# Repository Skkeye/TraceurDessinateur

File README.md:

# TraceurDessinateur
Projet Final Cegep

## Contexte/Origine
Le dessin est un art qui est difficile à apprendre et à maîtriser, alors l’option de prendre une photo pour décrire une scène devient très intéressante pour un artiste dépourvu de talent de dessinateur. Le TraceurDessinateur entre en jeu pour donner un compromis entre le dessin et la photo.

## Besoin General
Le besoin est de pouvoir dessiner un ou des objets sans pour autant avoir du talent pour dessiner. La partie cadrage et pinceau doivent être sans fil et rechargeable et doivent pouvoir être utilisés dans la majorité des environnements. La partie dessinateur doit être capable d'être configurable et facile à utiliser. 

## Objectif
L’objectif ici est de concevoir et de réaliser un pinceau 3d et une caméra de cadrage connectée par wifi au dessinateur qui lui pourra dessiner sur une feuille de papier.

## Fonctions Principales
La solution aura 3 parties principales en plus de la partie serveur qui connectera le tout. La première partie consiste d’une manette connectée au serveur par wifi, la deuxième d’une caméra qui détecte la position de la manette et la troisième d’un système de moteurs pas-à-pas pour dessiner sur une feuille de papier.
- La solution doit pouvoir voir et trouver la position de la manette via une caméra.
- La solution doit pouvoir choisir la couleur de la manette en fonction des couleurs perçus par la caméra.
- La solution doit pouvoir capter une force variable avec la manette.
- La solution doit consister d’une manette et d’une caméra portatives.
- La solution doit consister d’une manette et d’une caméra qui se connectent à un serveur WiFi dédié.
- La solution doit pouvoir dessiner à l'aide d’une machine CNC 2.5 axes.
- La solution doit être configurable via un menu contrôle avec un encodeur de rotation avec bouton.
- La solution doit avoir une caméra pour aider à positionner la caméra.
- La solution doit pouvoir être alimentée par une cellule LiPo pour la manette et la caméra.
- La solution doit avoir un bouton Marche/Arret sur le Dessinateur, la Caméra et la Manette.

## Contraintes
- Tension d’alimentation principale : 120 VAC
- Tension d’alimentation moteurs pas à pas : 4.1 VDC
- Tension d’alimentation de la caméra et la manette : 3.3v (LiPo 3.7v)
- Connexion sans fils : WiFi
- Application sur microcontrôleurs

## Livrables
- Produits Assembles : Manette, Camera, Dessinateur
- Logiciels installés sur les microcontrolleurs

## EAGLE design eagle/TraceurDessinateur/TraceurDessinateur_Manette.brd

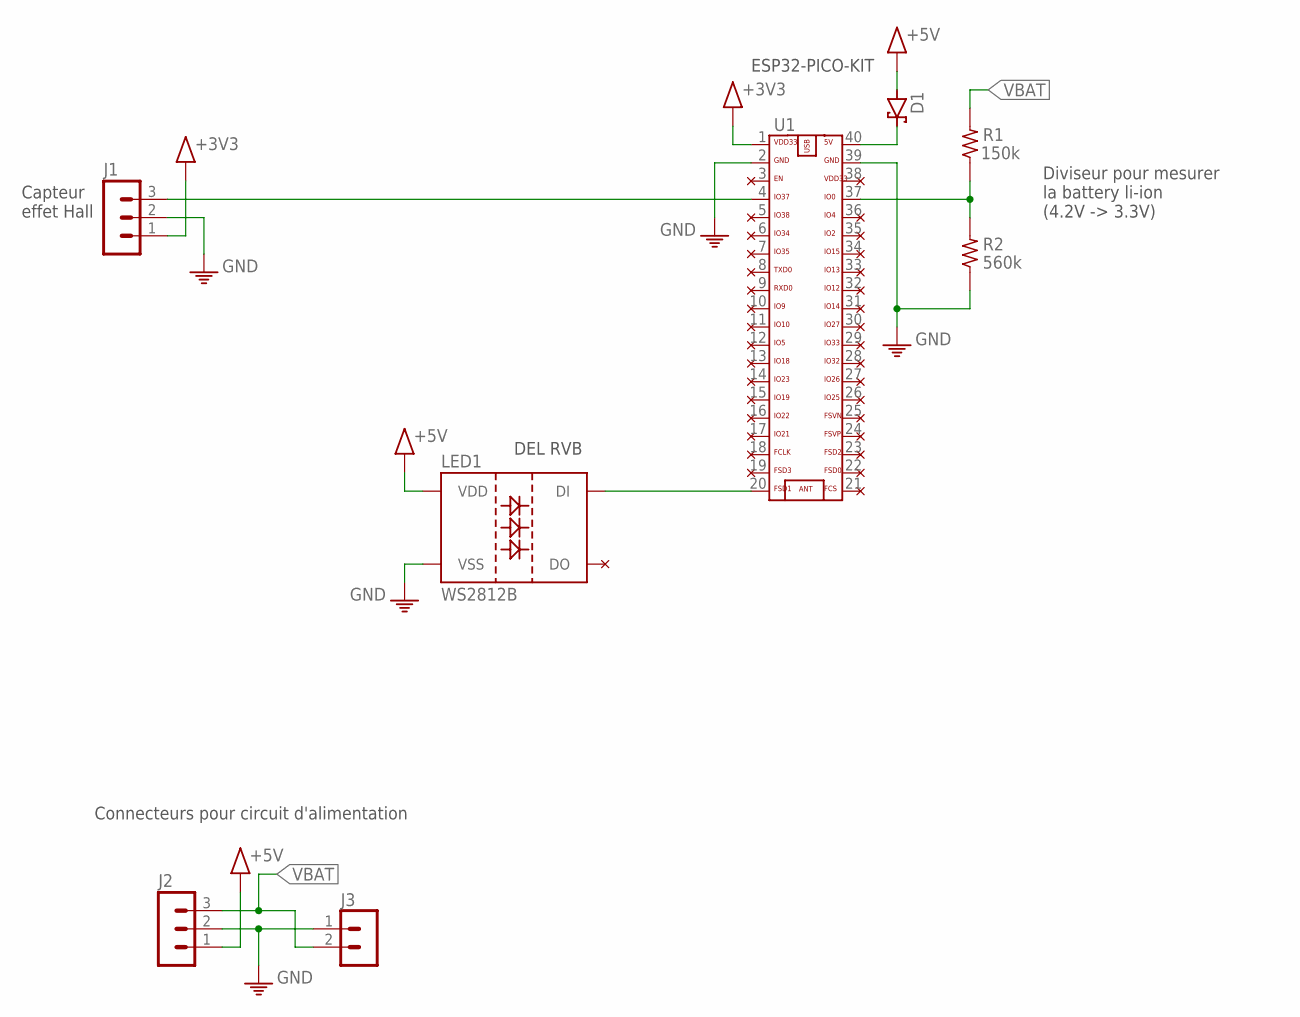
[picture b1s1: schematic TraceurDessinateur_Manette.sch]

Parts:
D1: 1N5817-B; DO41-7.6
J1, J2: MA03-1
J3: B2B-PH-K
LED1: WS2812B
R1: 150k; R1206W
R2: 560k; R1206W
U1: ESP32-PICO-V4-SOCKET

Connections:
+3V3: J1.1, U1.1 (3V3)
+5V: D1.A, J2.1, LED1.1 (VDD)
ADC_HALL: J1.3, U1.4
GND: J1.2, J2.2, J3.1, LED1.3 (VSS), R2.1, U1.2, U1.39
LED_DATA: LED1.4 (DI), U1.20
unnamed: D1.C, U1.40
VBAT: J2.3, J3.2, R1.2
VSENSE: R1.1, R2.2, U1.37

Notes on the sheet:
Capteur effet Hall
Connecteurs pour circuit d'alimentation
Diviseur pour mesurer la battery li-ion (4.2V -> 3.3V)
DEL RVB
ESP32-PICO-KIT

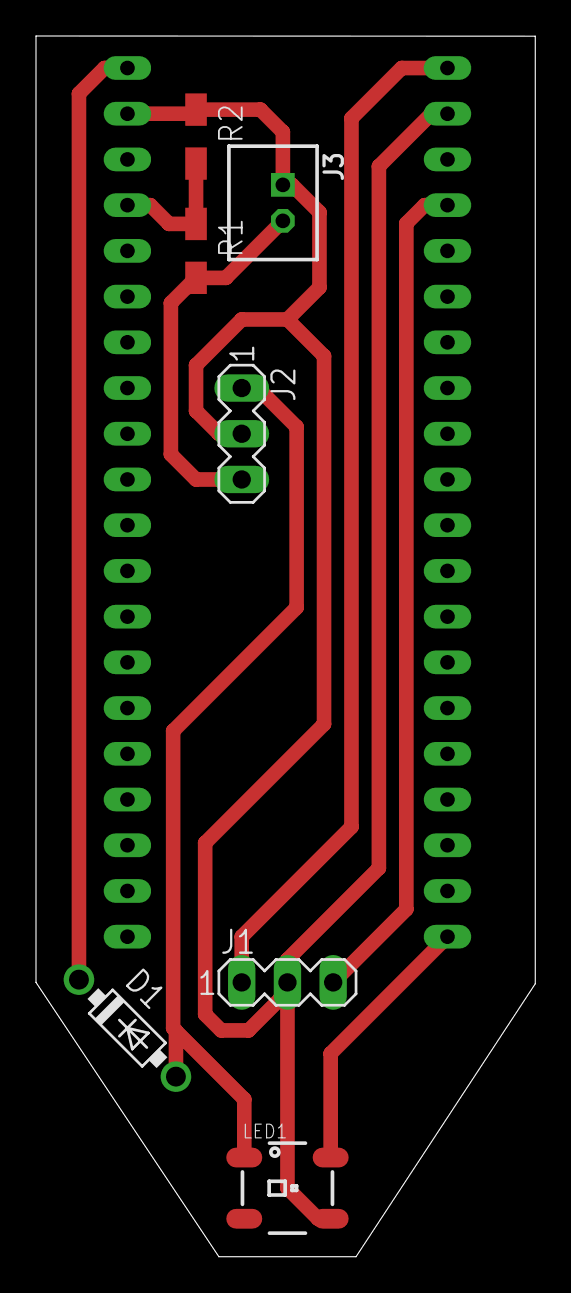
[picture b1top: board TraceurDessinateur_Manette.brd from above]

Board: 2 copper layers, 27.7 x 67.8 mm, 9 parts (1 on the bottom side), 8 nets.

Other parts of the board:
U$35: A3L-LOC

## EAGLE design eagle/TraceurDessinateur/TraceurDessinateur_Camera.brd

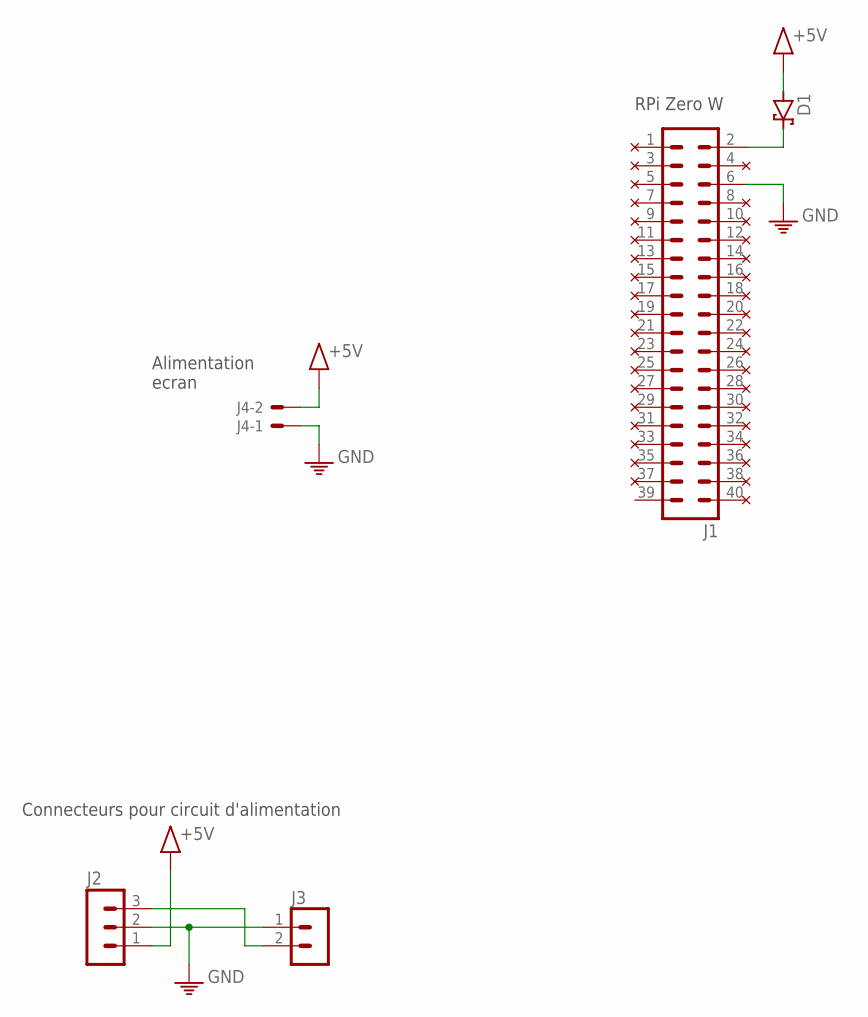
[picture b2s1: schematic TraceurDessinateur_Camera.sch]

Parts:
D1: 1N5817-B; DO41-7.6
J1: MA20-2
J2: MA03-1
J3: B2B-PH-K
J4: 22-23-2021

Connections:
+5V: D1.A, J2.1, J4.2
GND: J1.6, J2.2, J3.1, J4.1
unnamed: D1.C, J1.2
VBAT: J2.3, J3.2

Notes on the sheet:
RPi Zero W
Connecteurs pour circuit d'alimentation
Alimentation ecran

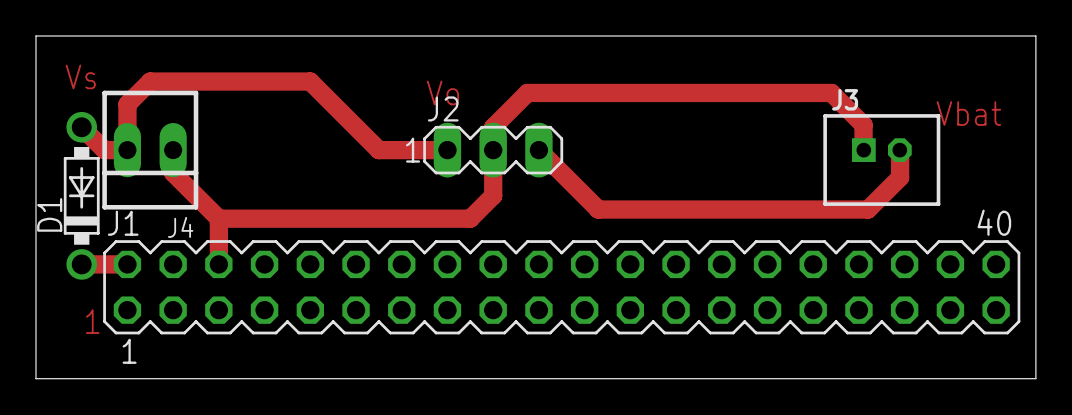
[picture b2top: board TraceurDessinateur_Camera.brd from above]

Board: 2 copper layers, 55.5 x 19.0 mm, 6 parts (0 on the bottom side), 4 nets.

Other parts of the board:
U$37: A3L-LOC

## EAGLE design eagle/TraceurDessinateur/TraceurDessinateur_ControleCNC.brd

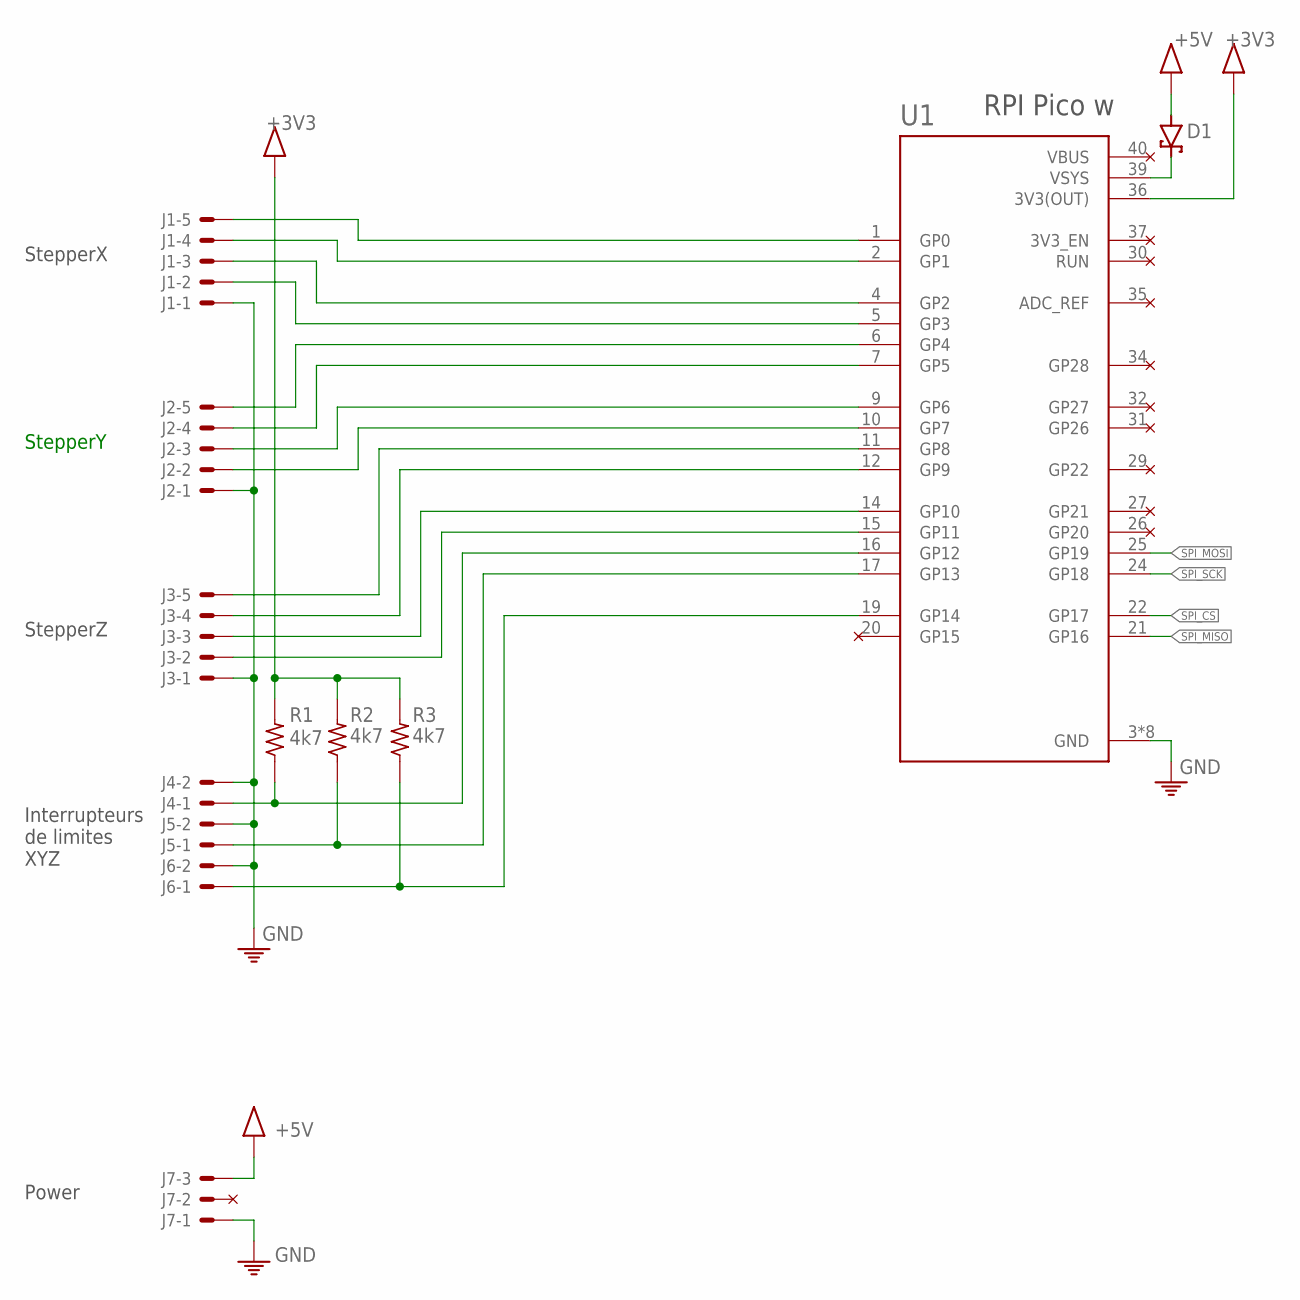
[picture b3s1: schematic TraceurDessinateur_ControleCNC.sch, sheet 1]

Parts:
D1: 1N5817-B; DO41-7.6
J1, J2, J3: 22-23-2051
J4, J5, J6: 22-23-2021
J7: 22-23-2031
R1, R2, R3: 4k7; R1206
U1: RASPBERRY_PICO-HEADERS-NO_DEBUGPICO-PKG-TH-NO_DEB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; PICO-PKG-TH-NO_DEBUG

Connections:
+3V3: R1.2, R2.2, R3.2, U1.36 (3V3(OUT)); also elsewhere on the board
+5V: D1.A, J7.3; also elsewhere on the board
GND: J1.1, J2.1, J3.1, J4.2, J5.2, J6.2, J7.1, U1.3 (GND), U1.8 (GND), U1.13 (GND), U1.18 (GND), U1.23 (GND), U1.28 (GND), U1.33 (GND), U1.38 (GND); also elsewhere on the board
unnamed: J1.5, U1.1 (GP0)
unnamed: J1.4, U1.2 (GP1)
unnamed: J1.3, U1.4 (GP2)
unnamed: J1.2, U1.5 (GP3)
unnamed: J2.5, U1.6 (GP4)
unnamed: J2.4, U1.7 (GP5)
unnamed: J2.3, U1.9 (GP6)
unnamed: J2.2, U1.10 (GP7)
unnamed: J3.5, U1.11 (GP8)
unnamed: J3.4, U1.12 (GP9)
unnamed: J3.3, U1.14 (GP10)
unnamed: J3.2, U1.15 (GP11)
unnamed: J4.1, R1.1, U1.16 (GP12)
unnamed: J5.1, R2.1, U1.17 (GP13)
unnamed: J6.1, R3.1, U1.19 (GP14)
unnamed: D1.C, U1.39 (VSYS)
SPI_CS: U1.22 (GP17); also elsewhere on the board
SPI_MISO: U1.21 (GP16); also elsewhere on the board
SPI_MOSI: U1.25 (GP19); also elsewhere on the board
SPI_SCK: U1.24 (GP18); also elsewhere on the board

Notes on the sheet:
StepperX
StepperY
StepperZ
Interrupteurs de limites XYZ
RPI Pico w
Power

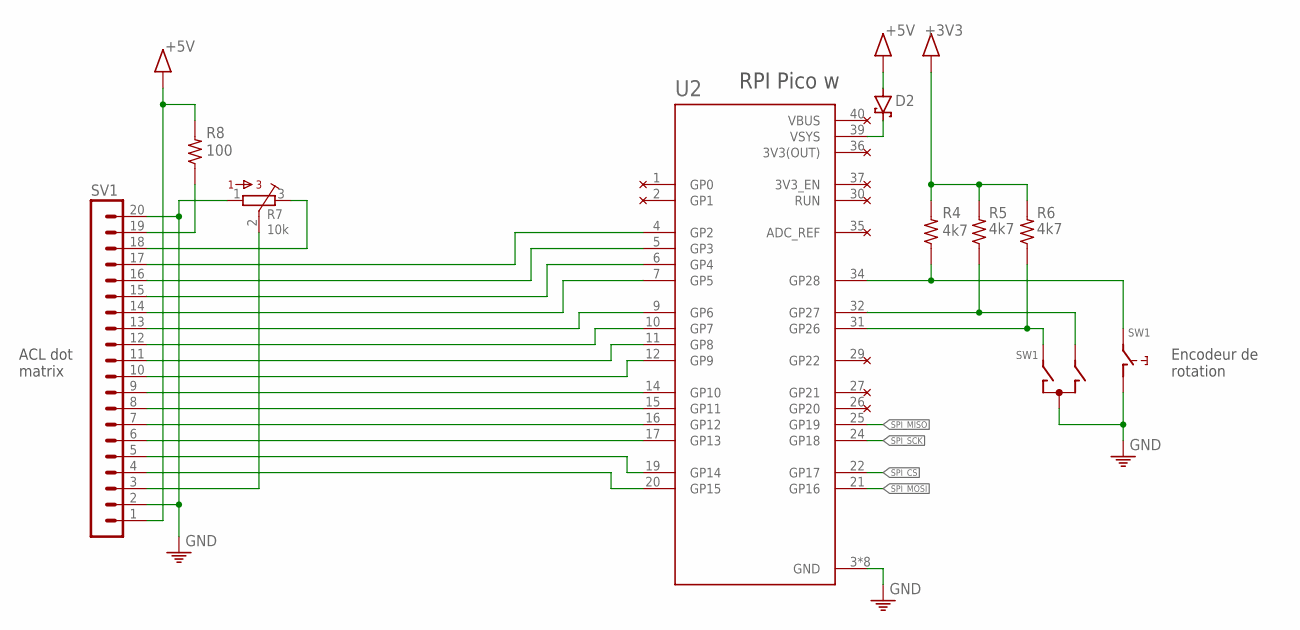
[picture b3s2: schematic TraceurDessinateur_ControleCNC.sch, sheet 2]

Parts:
D2: 1N5817-B; DO41-7.6
R4, R5, R6: 4k7; R1206
R7: 10k; 3362P
R8: 100; R1206
SV1: MA20-1
SW1: EC12E_SW; ALPS_EC12E_SW
U2: RASPBERRY_PICO-HEADERS-NO_DEBUGPICO-PKG-TH-NO_DEB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; PICO-PKG-TH-NO_DEBUG

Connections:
+3V3: R4.2, R5.2, R6.2; also elsewhere on the board
+5V: D2.A, R8.2, SV1.1; also elsewhere on the board
GND: U2.3 (GND), U2.8 (GND), U2.13 (GND), U2.18 (GND), U2.23 (GND), U2.28 (GND), U2.33 (GND), U2.38 (GND); also elsewhere on the board
unnamed: SV1.4, U2.20 (GP15)
unnamed: D2.C, U2.39 (VSYS)
unnamed: R6.1, SW1.A, U2.31 (GP26)
unnamed: R5.1, SW1.B, U2.32 (GP27)
unnamed: R4.1, SW1.E (2), U2.34 (GP28)
unnamed: SV1.5, U2.19 (GP14)
unnamed: SV1.6, U2.17 (GP13)
unnamed: SV1.7, U2.16 (GP12)
unnamed: SV1.8, U2.15 (GP11)
unnamed: SV1.9, U2.14 (GP10)
unnamed: SV1.10, U2.12 (GP9)
unnamed: SV1.11, U2.11 (GP8)
unnamed: SV1.12, U2.10 (GP7)
unnamed: SV1.13, U2.9 (GP6)
unnamed: SV1.14, U2.7 (GP5)
unnamed: SV1.15, U2.6 (GP4)
unnamed: SV1.16, U2.5 (GP3)
unnamed: SV1.17, U2.4 (GP2)
unnamed: R7.3, SV1.18
unnamed: R7.2, SV1.3
unnamed: R8.1, SV1.19
PE: R7.1, SV1.2, SV1.20, SW1.C, SW1.D (1)
SPI_CS: U2.22 (GP17); also elsewhere on the board
SPI_MISO: U2.25 (GP19); also elsewhere on the board
SPI_MOSI: U2.21 (GP16); also elsewhere on the board
SPI_SCK: U2.24 (GP18); also elsewhere on the board

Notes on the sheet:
ACL dot matrix
Encodeur de rotation
RPI Pico w

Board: 2 copper layers, 21 parts (0 on the bottom side), 45 nets, no tracks yet.

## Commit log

2023-01-23 Ajout de l'echeancier
2023-01-27 Update Echeancier
2023-01-30 update gantt
2023-02-28 Added CNC code
2023-02-28 quick update
2023-03-01 Python test code & code for CNC Steppers
2023-03-02 Cleanup et ajout de Doxygen
2023-03-13 Ajout du debugger
2023-04-08 chore: make test work for Dessinateur
2023-04-09 chore: at Celeste
2023-04-11 feat: Creation Code Manette final
2023-04-13 fix: DessinStepper is good
2023-04-13 feat: AllInOneDessinateur + MQTT
2023-04-18 feat: command menu; fix: fast IMU updates
2023-04-18 fix: last minute
2023-04-19 fix: reliable communication
2023-04-19 AHHHHHHH
2023-04-19 death
2023-04-25 help

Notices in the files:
parts and their libraries:
con-jst-ph: Copyright (C) 2016, Bob Starr
